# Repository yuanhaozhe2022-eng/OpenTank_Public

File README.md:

# OpenTank_Public
OpenTank board and code

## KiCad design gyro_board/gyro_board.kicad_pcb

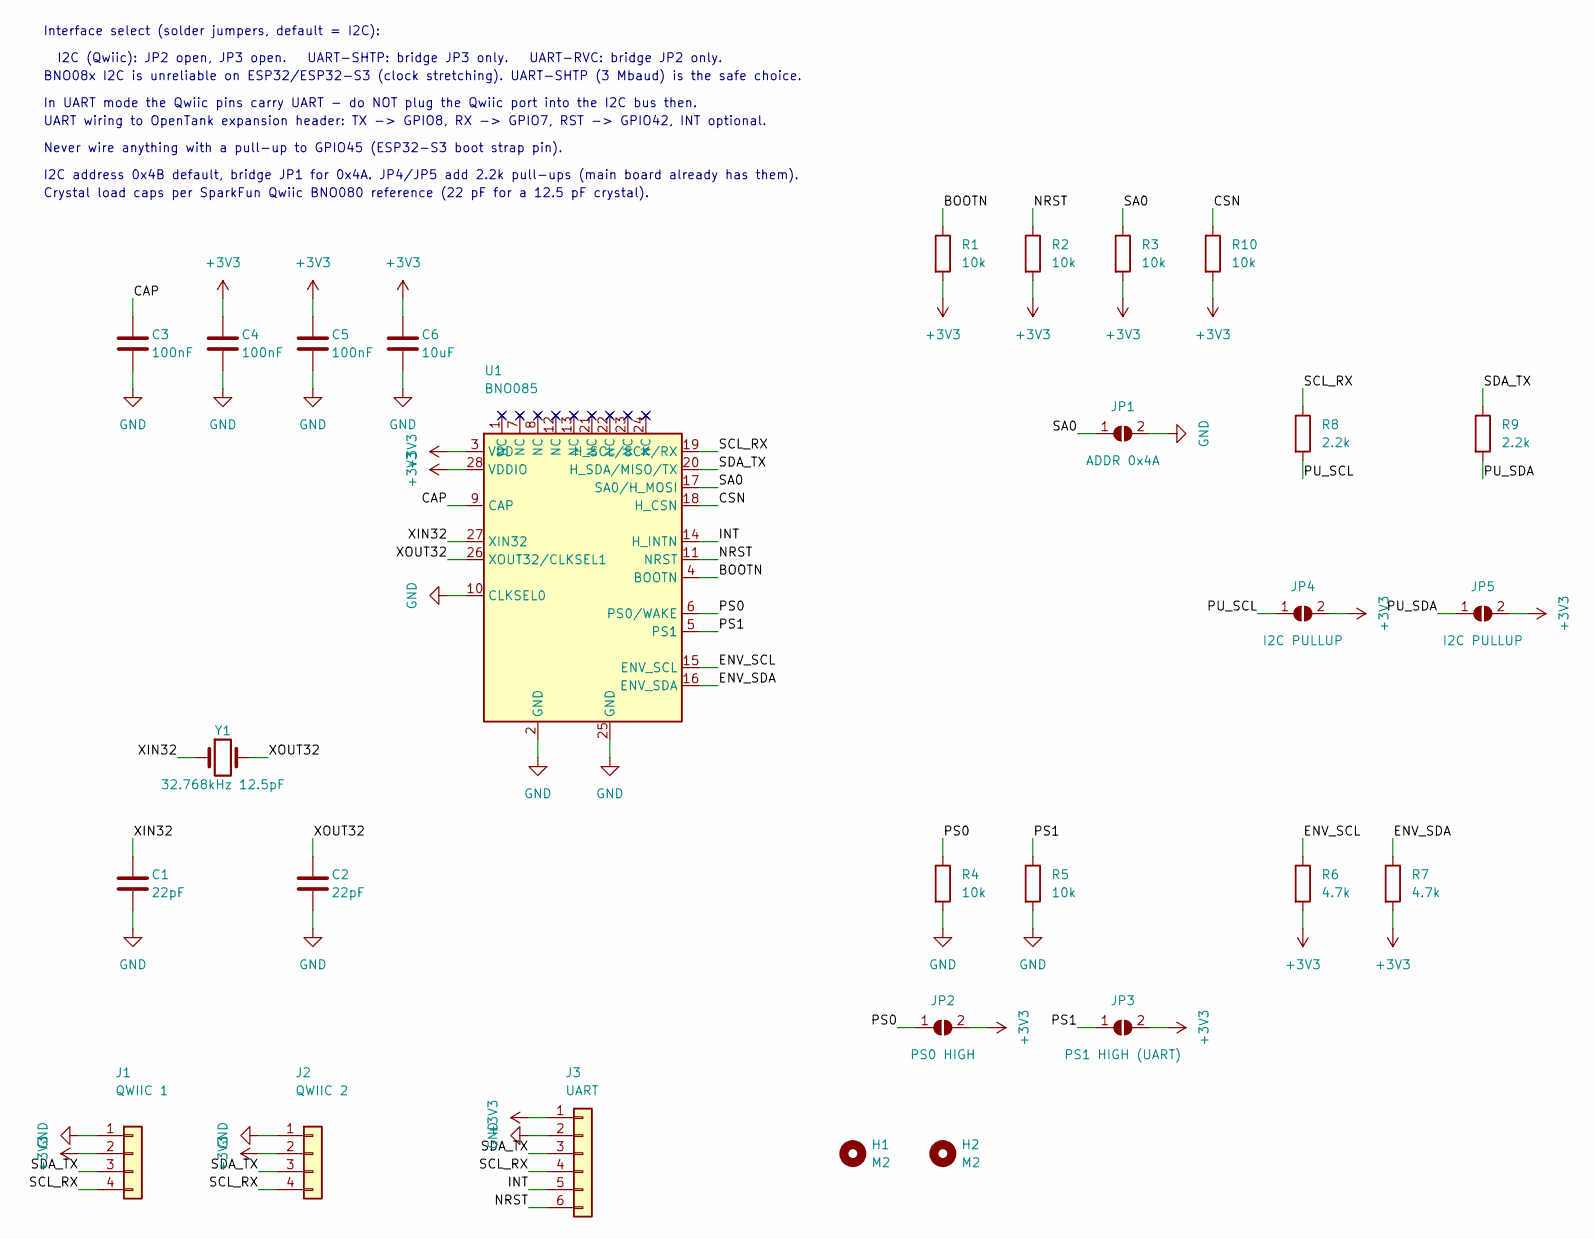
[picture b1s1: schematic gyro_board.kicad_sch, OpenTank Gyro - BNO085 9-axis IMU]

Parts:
C1, C2: 22pF; C_0603_1608Metric
C3, C4, C5: 100nF; C_0603_1608Metric
C6: 10uF; C_0805_2012Metric
H1, H2: M2; MountingHole_2.2mm_M2
J1: QWIIC 1; JST_SH_SM04B-SRSS-TB_1x04-1MP_P1.00mm_Horizontal; MPN JST SM04B-SRSS-TB
J2: QWIIC 2; JST_SH_SM04B-SRSS-TB_1x04-1MP_P1.00mm_Horizontal; MPN JST SM04B-SRSS-TB
J3: UART; PinHeader_1x06_P2.54mm_Vertical
JP1: ADDR 0x4A; SolderJumper-2_P1.3mm_Open_RoundedPad1.0x1.5mm
JP2: PS0 HIGH; SolderJumper-2_P1.3mm_Open_RoundedPad1.0x1.5mm
JP3: PS1 HIGH (UART); SolderJumper-2_P1.3mm_Open_RoundedPad1.0x1.5mm
JP4, JP5: I2C PULLUP; SolderJumper-2_P1.3mm_Open_RoundedPad1.0x1.5mm
R1, R2, R3, R4, R5, R10: 10k; R_0603_1608Metric
R6, R7: 4.7k; R_0603_1608Metric
R8, R9: 2.2k; R_0603_1608Metric
U1: BNO085; LGA-28_5.2x3.8mm_P0.5mm; MPN BNO085
Y1: 32.768kHz 12.5pF; Crystal_SMD_3215-2Pin_3.2x1.5mm; MPN ABS07-32.768KHZ-T

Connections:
+3V3: C4.1, C5.1, C6.1, J1.2, J2.2, J3.1, JP2.2 (B), JP3.2 (B), JP4.2 (B), JP5.2 (B), R1.2, R2.2, R3.2, R6.2, R7.2, R10.2, U1.3 (VDD), U1.28 (VDDIO)
/BOOTN: R1.1, U1.4 (BOOTN)
/CAP: C3.1, U1.9 (CAP)
/CSN: R10.1, U1.18 (H_CSN)
/ENV_SCL: R6.1, U1.15 (ENV_SCL)
/ENV_SDA: R7.1, U1.16 (ENV_SDA)
/INT: J3.5, U1.14 (H_INTN)
/NRST: J3.6, R2.1, U1.11 (NRST)
/PS0: JP2.1 (A), R4.1, U1.6 (PS0/WAKE)
/PS1: JP3.1 (A), R5.1, U1.5 (PS1)
/PU_SCL: JP4.1 (A), R8.2
/PU_SDA: JP5.1 (A), R9.2
/SA0: JP1.1 (A), R3.1, U1.17 (SA0/H_MOSI)
/SCL_RX: J1.4, J2.4, J3.4, R8.1, U1.19 (H_SCL/SCK/RX)
/SDA_TX: J1.3, J2.3, J3.3, R9.1, U1.20 (H_SDA/MISO/TX)
/XIN32: C1.1, U1.27 (XIN32), Y1.1
/XOUT32: C2.1, U1.26 (XOUT32/CLKSEL1), Y1.2
GND: C1.2, C2.2, C3.2, C4.2, C5.2, C6.2, J1.1, J2.1, J3.2, JP1.2 (B), R4.2, R5.2, U1.2 (GND), U1.10 (CLKSEL0), U1.25 (GND)

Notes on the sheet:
Interface select (solder jumpers, default = I2C):
I2C (Qwiic): JP2 open, JP3 open. UART-SHTP: bridge JP3 only. UART-RVC: bridge JP2 only.
BNO08x I2C is unreliable on ESP32/ESP32-S3 (clock stretching). UART-SHTP (3 Mbaud) is the safe choice.
In UART mode the Qwiic pins carry UART - do NOT plug the Qwiic port into the I2C bus then.
UART wiring to OpenTank expansion header: TX -> GPIO8, RX -> GPIO7, RST -> GPIO42, INT optional.
Never wire anything with a pull-up to GPIO45 (ESP32-S3 boot strap pin).
I2C address 0x4B default, bridge JP1 for 0x4A. JP4/JP5 add 2.2k pull-ups (main board already has them).
Crystal load caps per SparkFun Qwiic BNO080 reference (22 pF for a 12.5 pF crystal).

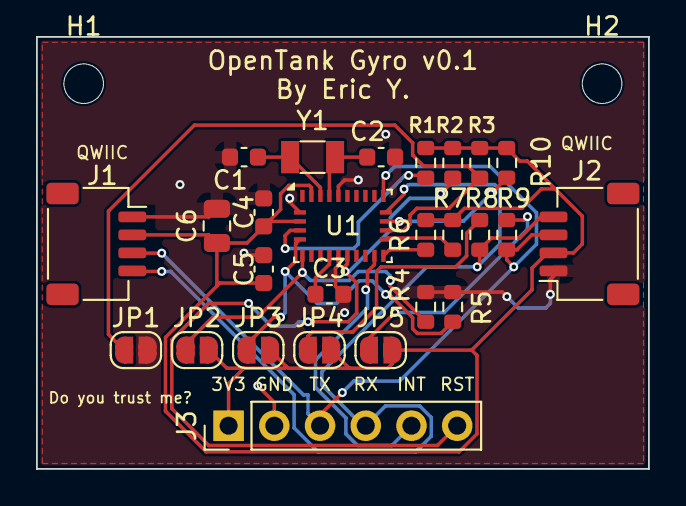
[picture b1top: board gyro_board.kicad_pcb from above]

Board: 2 copper layers, 34.0 x 24.0 mm, 28 parts (0 on the bottom side), 18 nets.

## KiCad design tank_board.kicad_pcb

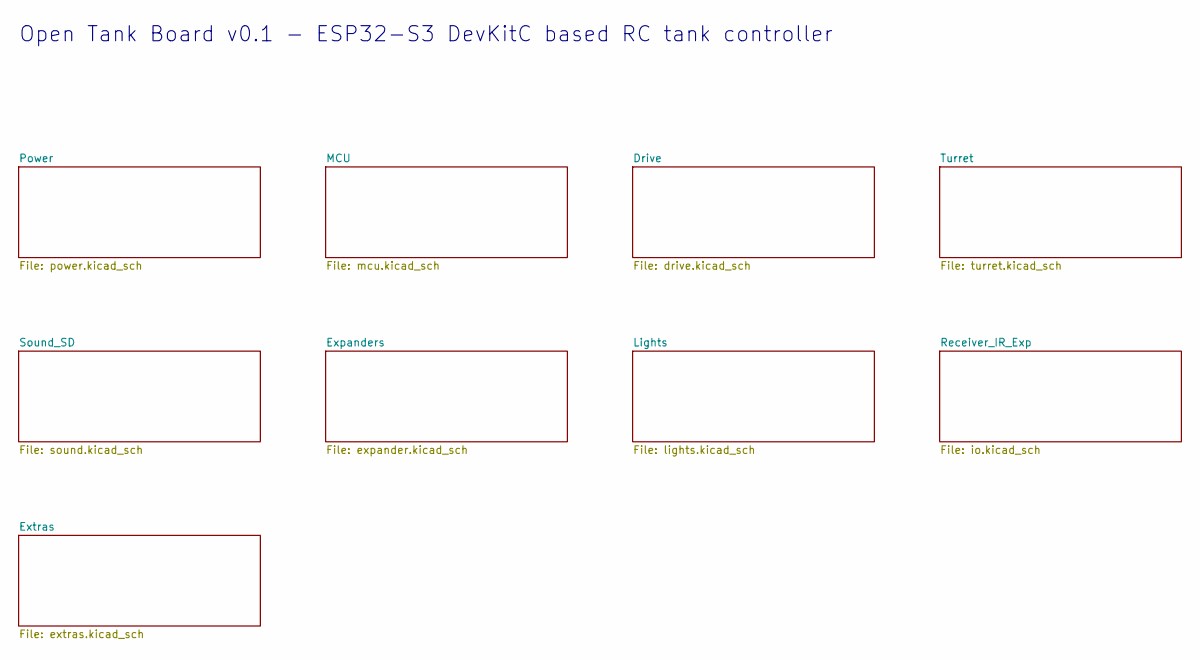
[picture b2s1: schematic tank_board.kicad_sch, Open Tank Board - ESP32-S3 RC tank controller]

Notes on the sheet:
Open Tank Board v0.1 - ESP32-S3 DevKitC based RC tank controller

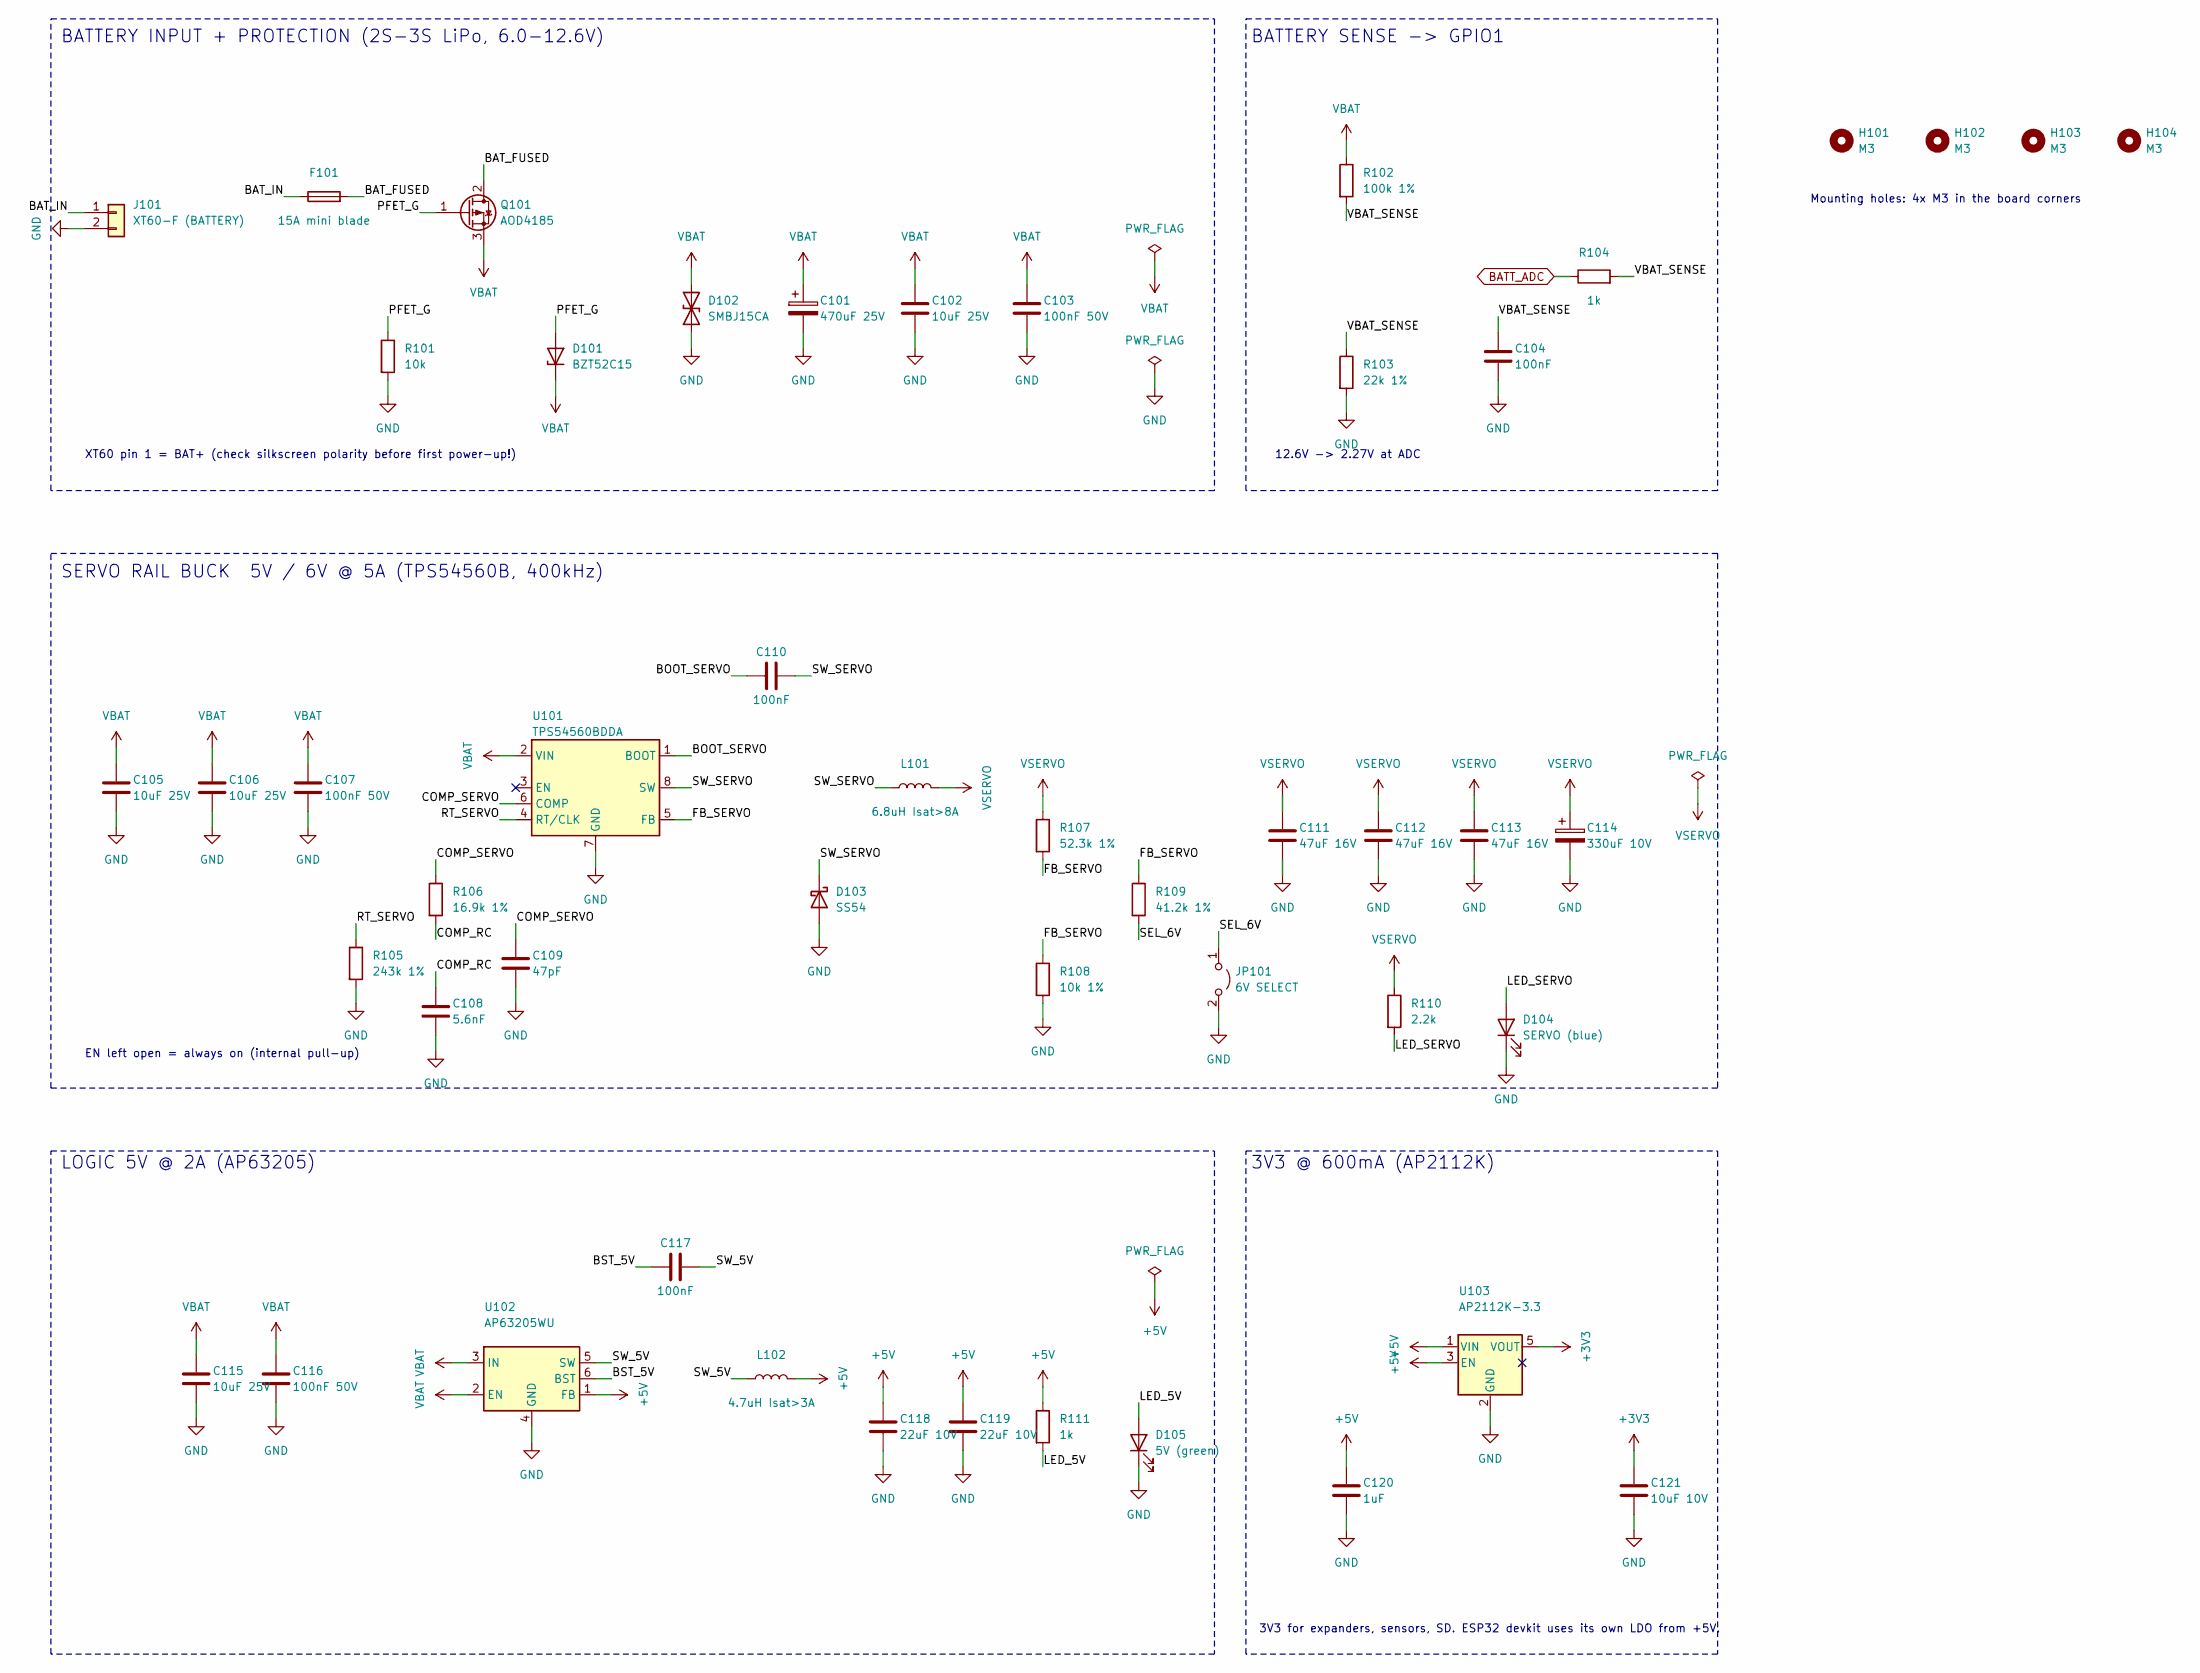
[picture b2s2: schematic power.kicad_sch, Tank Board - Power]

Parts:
C101: 470uF 25V; CP_Elec_10x10.5
C102, C105, C106, C115: 10uF 25V; C_1206_3216Metric
C103, C107, C116: 100nF 50V; C_0603_1608Metric
C104, C110, C117: 100nF; C_0603_1608Metric
C108: 5.6nF; C_0603_1608Metric
C109: 47pF; C_0603_1608Metric
C111, C112, C113: 47uF 16V; C_1210_3225Metric
C114: 330uF 10V; CP_Elec_6.3x7.7
C118, C119: 22uF 10V; C_1206_3216Metric
C120: 1uF; C_0603_1608Metric
C121: 10uF 10V; C_0805_2012Metric
D101: BZT52C15; D_SOD-123; MPN BZT52C15
D102: SMBJ15CA; D_SMB; MPN SMBJ15CA
D103: SS54; D_SMC; MPN SS54 (40V 5A)
D104: SERVO (blue); LED_0603_1608Metric
D105: 5V (green); LED_0603_1608Metric
F101: 15A mini blade; Fuseholder_Blade_Mini_Keystone_3568; MPN Keystone 3568 + 15A ATM fuse
H101, H102, H103, H104: M3; MountingHole_3.2mm_M3
J101: XT60-F (BATTERY); AMASS_XT60-F_1x02_P7.20mm_Vertical; MPN AMASS XT60-F
JP101: 6V SELECT; PinHeader_1x02_P2.54mm_Vertical
L101: 6.8uH Isat>8A; L_Bourns_SRP1038C_10.0x10.0mm; MPN Bourns SRP1038C-6R8M
L102: 4.7uH Isat>3A; L_Bourns_SRP5030T; MPN Bourns SRP5030T-4R7M
Q101: AOD4185; TO-252-2; MPN AOD4185
R101: 10k; R_0603_1608Metric
R102: 100k 1%; R_0603_1608Metric
R103: 22k 1%; R_0603_1608Metric
R104, R111: 1k; R_0603_1608Metric
R105: 243k 1%; R_0603_1608Metric
R106: 16.9k 1%; R_0603_1608Metric
R107: 52.3k 1%; R_0603_1608Metric
R108: 10k 1%; R_0603_1608Metric
R109: 41.2k 1%; R_0603_1608Metric
R110: 2.2k; R_0603_1608Metric
U101: TPS54560BDDA; Texas_R-PDSO-G8_EP2.95x4.9mm_Mask2.4x3.1mm_ThermalVias; MPN TPS54560BDDAR
U102: AP63205WU; TSOT-23-6; MPN AP63205WU-7
U103: AP2112K-3.3; SOT-23-5; MPN AP2112K-3.3TRG1

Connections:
+3V3: C121.1, U103.5 (VOUT); also elsewhere on the board
+5V: C118.1, C119.1, C120.1, L102.2, R111.1, U102.1 (FB), U103.1 (VIN), U103.3 (EN); also elsewhere on the board
/Power/BAT_FUSED: F101.2, Q101.2 (D)
/Power/BAT_IN: F101.1, J101.1
/Power/BOOT_SERVO: C110.1, U101.1 (BOOT)
/Power/BST_5V: C117.1, U102.6 (BST)
/Power/COMP_RC: C108.1, R106.2
/Power/COMP_SERVO: C109.1, R106.1, U101.6 (COMP)
/Power/FB_SERVO: R107.2, R108.1, R109.1, U101.5 (FB)
/Power/LED_5V: D105.2 (A), R111.2
/Power/LED_SERVO: D104.2 (A), R110.2
/Power/PFET_G: D101.2 (A), Q101.1 (G), R101.1
/Power/RT_SERVO: R105.1, U101.4 (RT/CLK)
/Power/SEL_6V: JP101.1 (A), R109.2
/Power/SW_5V: C117.2, L102.1, U102.5 (SW)
/Power/SW_SERVO: C110.2, D103.1 (K), L101.1, U101.8 (SW)
/Power/VBAT_SENSE: C104.1, R102.2, R103.1, R104.2
BATT_ADC: R104.1; also elsewhere on the board
GND: C101.2, C102.2, C103.2, C104.2, C105.2, C106.2, C107.2, C108.2, C109.2, C111.2, C112.2, C113.2, C114.2, C115.2, C116.2, C118.2, C119.2, C120.2, C121.2, D102.1 (A1), D103.2 (A), D104.1 (K), D105.1 (K), J101.2, JP101.2 (B), R101.2, R103.2, R105.2, R108.2, U101.7 (GND), U101.9 (GND), U102.4 (GND), U103.2 (GND); also elsewhere on the board
VBAT: C101.1, C102.1, C103.1, C105.1, C106.1, C107.1, C115.1, C116.1, D101.1 (K), D102.2 (A2), Q101.3 (S), R102.1, U101.2 (VIN), U102.2 (EN), U102.3 (IN); also elsewhere on the board
VSERVO: C111.1, C112.1, C113.1, C114.1, L101.2, R107.1, R110.1; also elsewhere on the board

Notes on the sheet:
BATTERY INPUT + PROTECTION (2S-3S LiPo, 6.0-12.6V)
XT60 pin 1 = BAT+ (check silkscreen polarity before first power-up!)
BATTERY SENSE -> GPIO1
12.6V -> 2.27V at ADC
SERVO RAIL BUCK 5V / 6V @ 5A (TPS54560B, 400kHz)
EN left open = always on (internal pull-up)
LOGIC 5V @ 2A (AP63205)
3V3 @ 600mA (AP2112K)
3V3 for expanders, sensors, SD. ESP32 devkit uses its own LDO from +5V.
Mounting holes: 4x M3 in the board corners

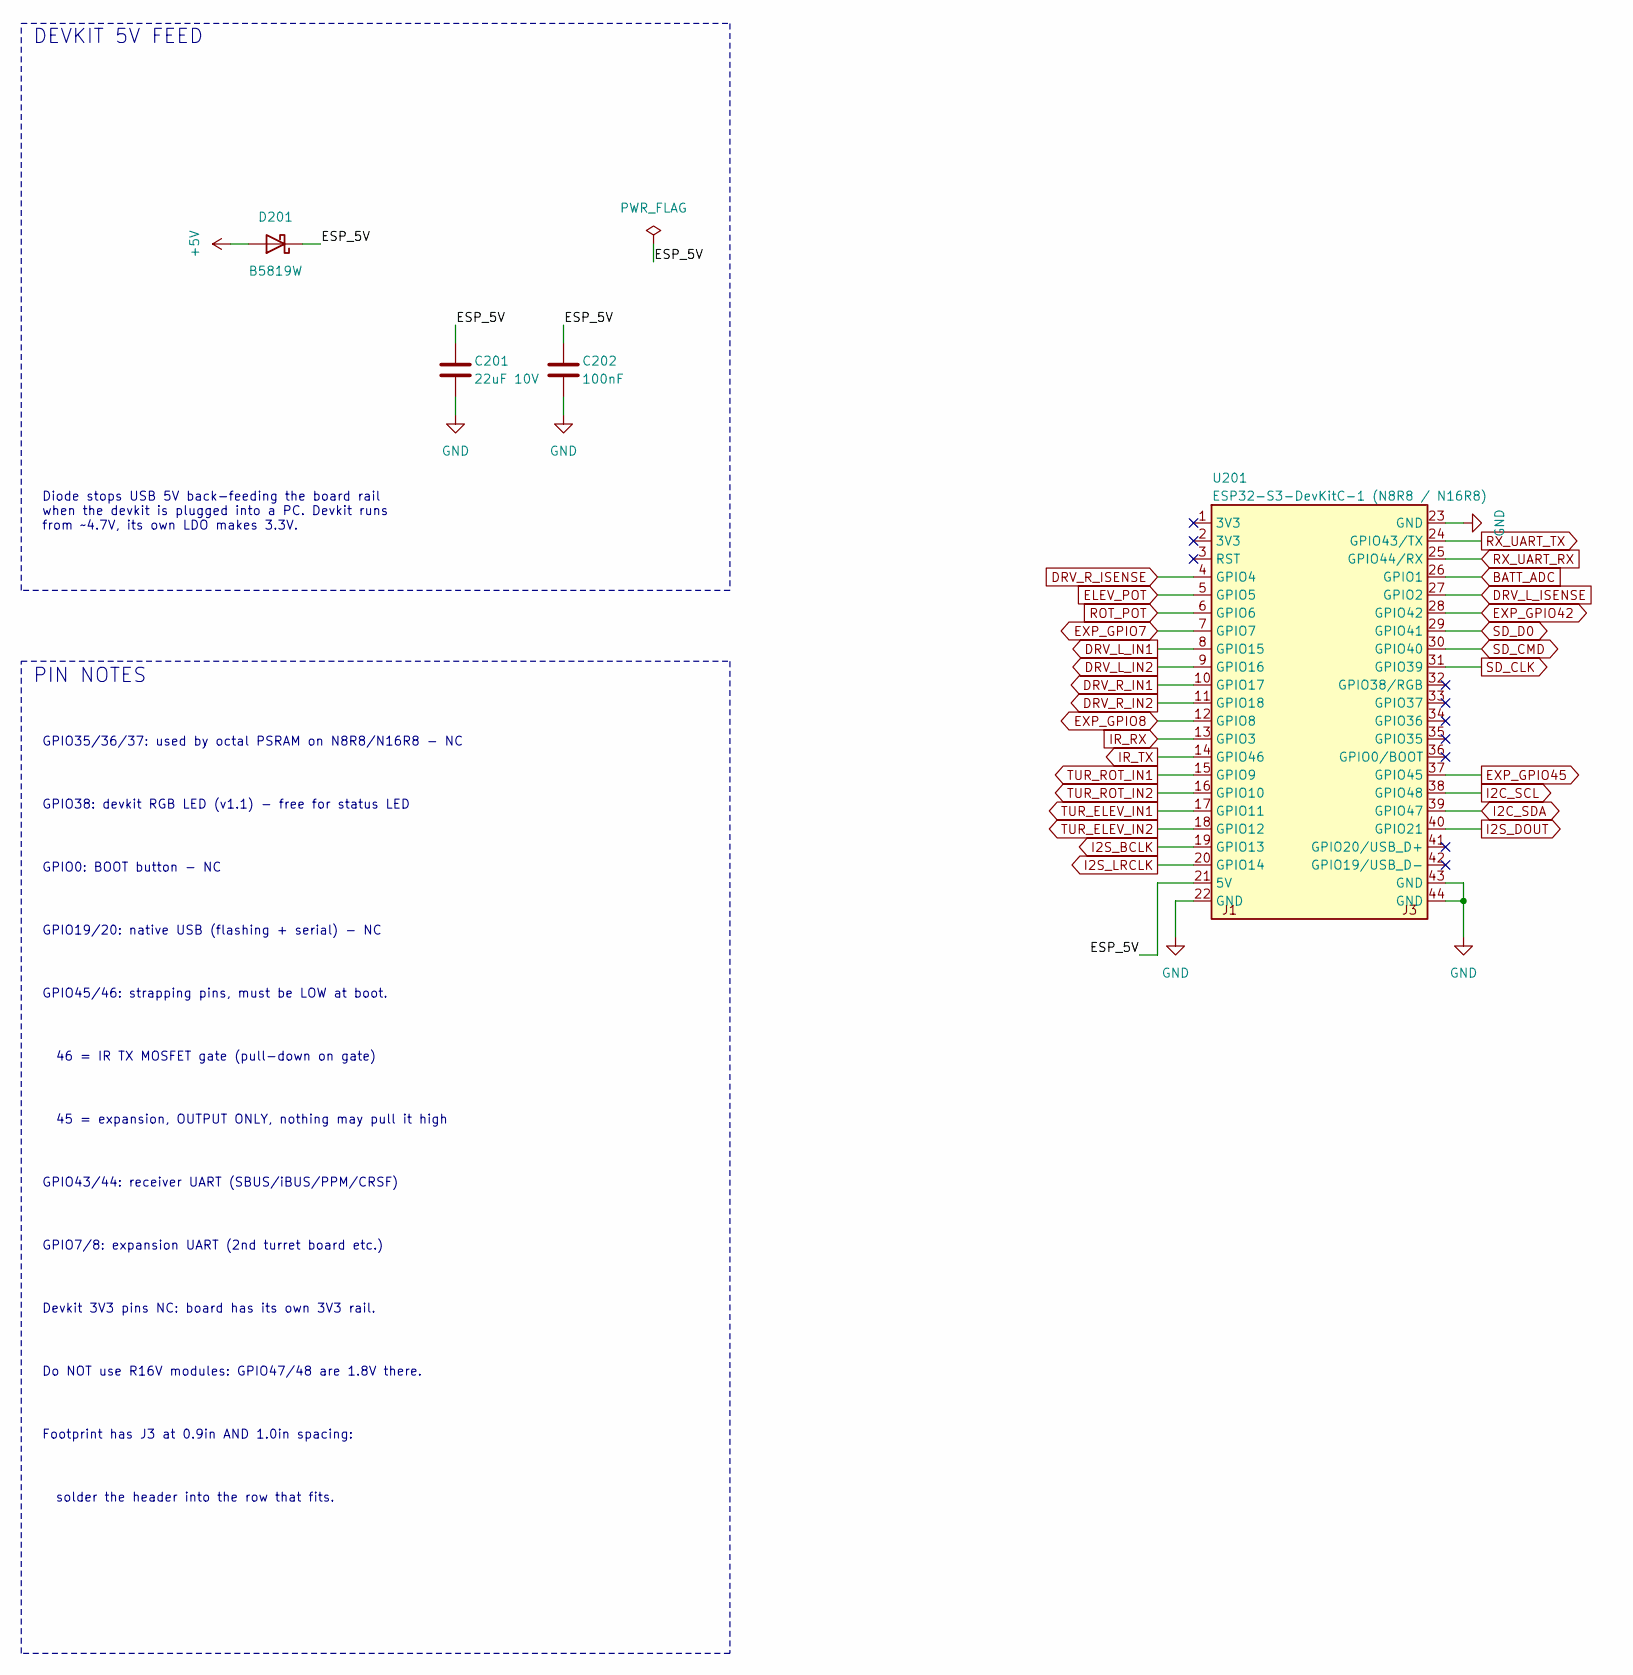
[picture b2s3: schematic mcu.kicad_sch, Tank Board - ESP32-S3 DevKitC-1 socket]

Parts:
C201: 22uF 10V; C_1206_3216Metric
C202: 100nF; C_0603_1608Metric
D201: B5819W; D_SOD-123; MPN B5819W (40V 1A)
U201: ESP32-S3-DevKitC-1 (N8R8 / N16R8); ESP32-S3-DevKitC-1_Socket; MPN ESP32-S3-DevKitC-1 + 2x 1x22 female hea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

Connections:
+5V: D201.2 (A); also elsewhere on the board
/MCU/ESP_5V: C201.1, C202.1, D201.1 (K), U201.21 (5V)
BATT_ADC: U201.26 (GPIO1); also elsewhere on the board
DRV_L_IN1: U201.8 (GPIO15); also elsewhere on the board
DRV_L_IN2: U201.9 (GPIO16); also elsewhere on the board
DRV_L_ISENSE: U201.27 (GPIO2); also elsewhere on the board
DRV_R_IN1: U201.10 (GPIO17); also elsewhere on the board
DRV_R_IN2: U201.11 (GPIO18); also elsewhere on the board
DRV_R_ISENSE: U201.4 (GPIO4); also elsewhere on the board
ELEV_POT: U201.5 (GPIO5); also elsewhere on the board
EXP_GPIO7: U201.7 (GPIO7); also elsewhere on the board
EXP_GPIO8: U201.12 (GPIO8); also elsewhere on the board
EXP_GPIO42: U201.28 (GPIO42); also elsewhere on the board
EXP_GPIO45: U201.37 (GPIO45); also elsewhere on the board
GND: C201.2, C202.2, U201.22 (GND), U201.23 (GND), U201.43 (GND), U201.44 (GND); also elsewhere on the board
I2C_SCL: U201.38 (GPIO48); also elsewhere on the board
I2C_SDA: U201.39 (GPIO47); also elsewhere on the board
I2S_BCLK: U201.19 (GPIO13); also elsewhere on the board
I2S_DOUT: U201.40 (GPIO21); also elsewhere on the board
I2S_LRCLK: U201.20 (GPIO14); also elsewhere on the board
IR_RX: U201.13 (GPIO3); also elsewhere on the board
IR_TX: U201.14 (GPIO46); also elsewhere on the board
ROT_POT: U201.6 (GPIO6); also elsewhere on the board
RX_UART_RX: U201.25 (GPIO44/RX); also elsewhere on the board
RX_UART_TX: U201.24 (GPIO43/TX); also elsewhere on the board
SD_CLK: U201.31 (GPIO39); also elsewhere on the board
SD_CMD: U201.30 (GPIO40); also elsewhere on the board
SD_D0: U201.29 (GPIO41); also elsewhere on the board
TUR_ELEV_IN1: U201.17 (GPIO11); also elsewhere on the board
TUR_ELEV_IN2: U201.18 (GPIO12); also elsewhere on the board
TUR_ROT_IN1: U201.15 (GPIO9); also elsewhere on the board
TUR_ROT_IN2: U201.16 (GPIO10); also elsewhere on the board

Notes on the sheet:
DEVKIT 5V FEED
Diode stops USB 5V back-feeding the board rail when the devkit is plugged into a PC. Devkit runs from ~4.7V, its own LDO makes 3.3V.
PIN NOTES
GPIO35/36/37: used by octal PSRAM on N8R8/N16R8 - NC
GPIO38: devkit RGB LED (v1.1) - free for status LED
GPIO0: BOOT button - NC
GPIO19/20: native USB (flashing + serial) - NC
GPIO45/46: strapping pins, must be LOW at boot.
46 = IR TX MOSFET gate (pull-down on gate)
45 = expansion, OUTPUT ONLY, nothing may pull it high
GPIO43/44: receiver UART (SBUS/iBUS/PPM/CRSF)
GPIO7/8: expansion UART (2nd turret board etc.)
Devkit 3V3 pins NC: board has its own 3V3 rail.
Do NOT use R16V modules: GPIO47/48 are 1.8V there.
Footprint has J3 at 0.9in AND 1.0in spacing:
solder the header into the row that fits.

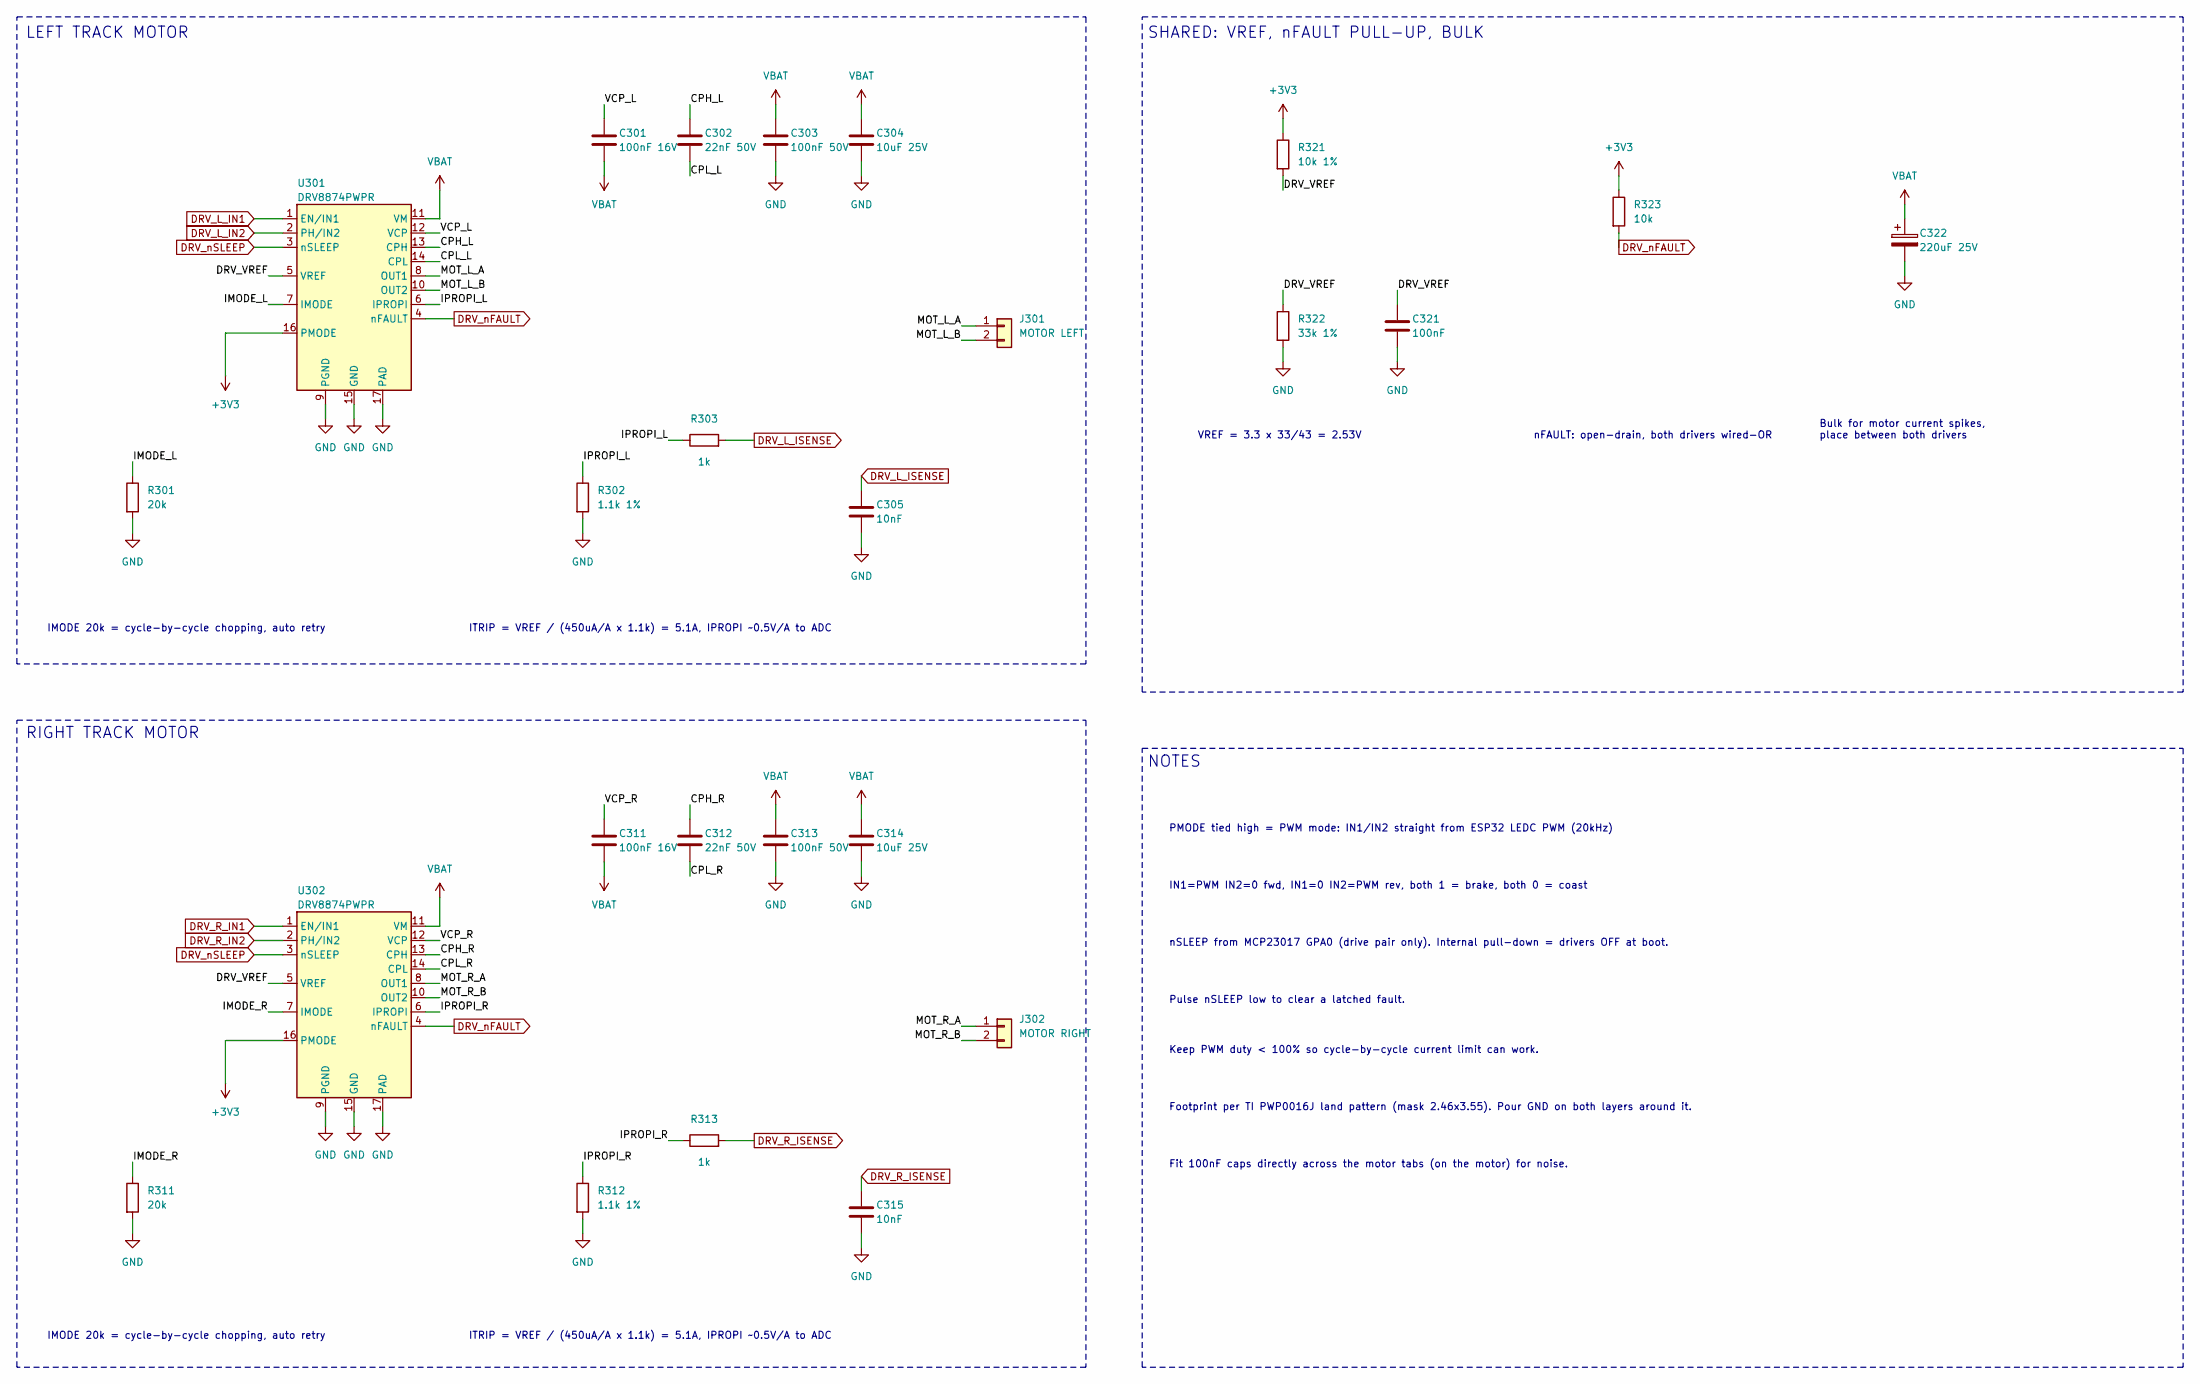
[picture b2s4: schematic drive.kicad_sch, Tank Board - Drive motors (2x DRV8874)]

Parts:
C301, C311: 100nF 16V; C_0603_1608Metric
C302, C312: 22nF 50V; C_0603_1608Metric
C303, C313: 100nF 50V; C_0603_1608Metric
C304, C314: 10uF 25V; C_1206_3216Metric
C305, C315: 10nF; C_0603_1608Metric
C321: 100nF; C_0603_1608Metric
C322: 220uF 25V; CP_Elec_10x10.5
J301: MOTOR LEFT; TerminalBlock_Phoenix_MKDS-1,5-2-5.08_1x02_P5.08mm_Horizont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; MPN 5.08mm 2-pos screw terminal
J302: MOTOR RIGHT; TerminalBlock_Phoenix_MKDS-1,5-2-5.08_1x02_P5.08mm_Horizont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; MPN 5.08mm 2-pos screw terminal
R301, R311: 20k; R_0603_1608Metric
R302, R312: 1.1k 1%; R_0603_1608Metric
R303, R313: 1k; R_0603_1608Metric
R321: 10k 1%; R_0603_1608Metric
R322: 33k 1%; R_0603_1608Metric
R323: 10k; R_0603_1608Metric
U301, U302: DRV8874PWPR; DRV887x_HTSSOP-16_PWP0016J_ThermalVias; MPN DRV8874PWPR

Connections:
+3V3: R321.1, R323.1, U301.16 (PMODE), U302.16 (PMODE); also elsewhere on the board
/Drive/CPH_L: C302.1, U301.13 (CPH)
/Drive/CPH_R: C312.1, U302.13 (CPH)
/Drive/CPL_L: C302.2, U301.14 (CPL)
/Drive/CPL_R: C312.2, U302.14 (CPL)
/Drive/DRV_VREF: C321.1, R321.2, R322.1, U301.5 (VREF), U302.5 (VREF)
/Drive/IMODE_L: R301.1, U301.7 (IMODE)
/Drive/IMODE_R: R311.1, U302.7 (IMODE)
/Drive/IPROPI_L: R302.1, R303.1, U301.6 (IPROPI)
/Drive/IPROPI_R: R312.1, R313.1, U302.6 (IPROPI)
/Drive/MOT_L_A: J301.1, U301.8 (OUT1)
/Drive/MOT_L_B: J301.2, U301.10 (OUT2)
/Drive/MOT_R_A: J302.1, U302.8 (OUT1)
/Drive/MOT_R_B: J302.2, U302.10 (OUT2)
/Drive/VCP_L: C301.1, U301.12 (VCP)
/Drive/VCP_R: C311.1, U302.12 (VCP)
DRV_L_IN1: U301.1 (EN/IN1); also elsewhere on the board
DRV_L_IN2: U301.2 (PH/IN2); also elsewhere on the board
DRV_L_ISENSE: C305.1, R303.2; also elsewhere on the board
DRV_R_IN1: U302.1 (EN/IN1); also elsewhere on the board
DRV_R_IN2: U302.2 (PH/IN2); also elsewhere on the board
DRV_R_ISENSE: C315.1, R313.2; also elsewhere on the board
DRV_nFAULT: R323.2, U301.4 (nFAULT), U302.4 (nFAULT); also elsewhere on the board
DRV_nSLEEP: U301.3 (nSLEEP), U302.3 (nSLEEP); also elsewhere on the board
GND: C303.2, C304.2, C305.2, C313.2, C314.2, C315.2, C321.2, C322.2, R301.2, R302.2, R311.2, R312.2, R322.2, U301.9 (PGND), U301.15 (GND), U301.17 (PAD), U302.9 (PGND), U302.15 (GND), U302.17 (PAD); also elsewhere on the board
VBAT: C301.2, C303.1, C304.1, C311.2, C313.1, C314.1, C322.1, U301.11 (VM), U302.11 (VM); also elsewhere on the board

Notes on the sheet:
LEFT TRACK MOTOR
IMODE 20k = cycle-by-cycle chopping, auto retry
ITRIP = VREF / (450uA/A x 1.1k) = 5.1A, IPROPI ~0.5V/A to ADC
RIGHT TRACK MOTOR
SHARED: VREF, nFAULT PULL-UP, BULK
VREF = 3.3 x 33/43 = 2.53V
nFAULT: open-drain, both drivers wired-OR
Bulk for motor current spikes, place between both drivers
NOTES
PMODE tied high = PWM mode: IN1/IN2 straight from ESP32 LEDC PWM (20kHz)
IN1=PWM IN2=0 fwd, IN1=0 IN2=PWM rev, both 1 = brake, both 0 = coast
nSLEEP from MCP23017 GPA0 (drive pair only). Internal pull-down = drivers OFF at boot.
Pulse nSLEEP low to clear a latched fault.
Keep PWM duty < 100% so cycle-by-cycle current limit can work.
Footprint per TI PWP0016J land pattern (mask 2.46x3.55). Pour GND on both layers around it.
Fit 100nF caps directly across the motor tabs (on the motor) for noise.
